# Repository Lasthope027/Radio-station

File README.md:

# 100 MHz FM Transmitter

## Overview

This repository contains the design and simulation files for a **100 MHz FM transmitter**, including the transmitter circuit, PCB design, manufacturing files, and a dedicated 100 MHz antenna design.

The project covers the workflow from **circuit simulation and PCB design to antenna modeling**.

For detailed technical specifications, design methodology, calculations, and simulation results, refer to the **[FM Radio Transmitter.pdf](FM%20Radio%20Transmitter.pdf)** included in this repository.

---

## Repository Structure

The repository is organized into the following sections:

- **Antenna/** — Contains the 100 MHz antenna model.
- **Transmitter/** — Contains the LTspice transmitter circuit and KiCad PCB design files.
- **FM Radio Transmitter.pdf** — Contains the detailed technical documentation and simulation results.
- **README.md** — Provides an overview and guide to the repository.

---

## Antenna

The `Antenna/` folder contains the antenna model designed specifically for operation at **100 MHz**.

### File

`FM Antenna.maa`

The `.maa` file can be opened using **MMANA-GAL** to inspect and simulate the antenna design.

**Software:** MMANA-GAL

---

## Transmitter

The `Transmitter/` folder contains the transmitter circuit and PCB design files.

### LTspice Circuit

The `Circuit .asc` file contains the transmitter schematic and can be opened using **LTspice** to inspect the circuit and reproduce the simulation.

**Software:** LTspice

### KiCad Files

The `KiCad/` folder contains the schematic, PCB layout, and manufacturing files.

- `RF Transmitter.kicad_sch` — KiCad schematic
- `RF Transmitter.kicad_pcb` — PCB layout
- `Gerber.zip` — Gerber files prepared for PCB fabrication

**Software:** KiCad

---

## Documentation

The `FM Radio Transmitter.pdf` contains the detailed technical documentation of the project, including the design, calculations, circuit analysis, simulation results, and antenna analysis.

For complete technical details, refer to the **[FM Radio Transmitter.pdf](FM%20Radio%20Transmitter.pdf)**.

---

## Software Used

| Software | Purpose |
|---|---|
| **LTspice** | Transmitter circuit design and simulation |
| **KiCad** | Schematic and PCB design |
| **MMANA-GAL** | 100 MHz antenna modeling and simulation |

---

## How to Explore the Repository

- To inspect the **transmitter circuit**, open the `.asc` file using LTspice.
- To inspect the **PCB schematic**, open the `.kicad_sch` file using KiCad.
- To inspect the **PCB layout**, open the `.kicad_pcb` file using KiCad.
- To fabricate the PCB, use the **Gerber.zip** manufacturing files.
- To inspect the **100 MHz antenna**, open the `.maa` file using MMANA-GAL.
- For detailed technical specifications, calculations, and simulation results, refer to the **FM Radio Transmitter PDF**.

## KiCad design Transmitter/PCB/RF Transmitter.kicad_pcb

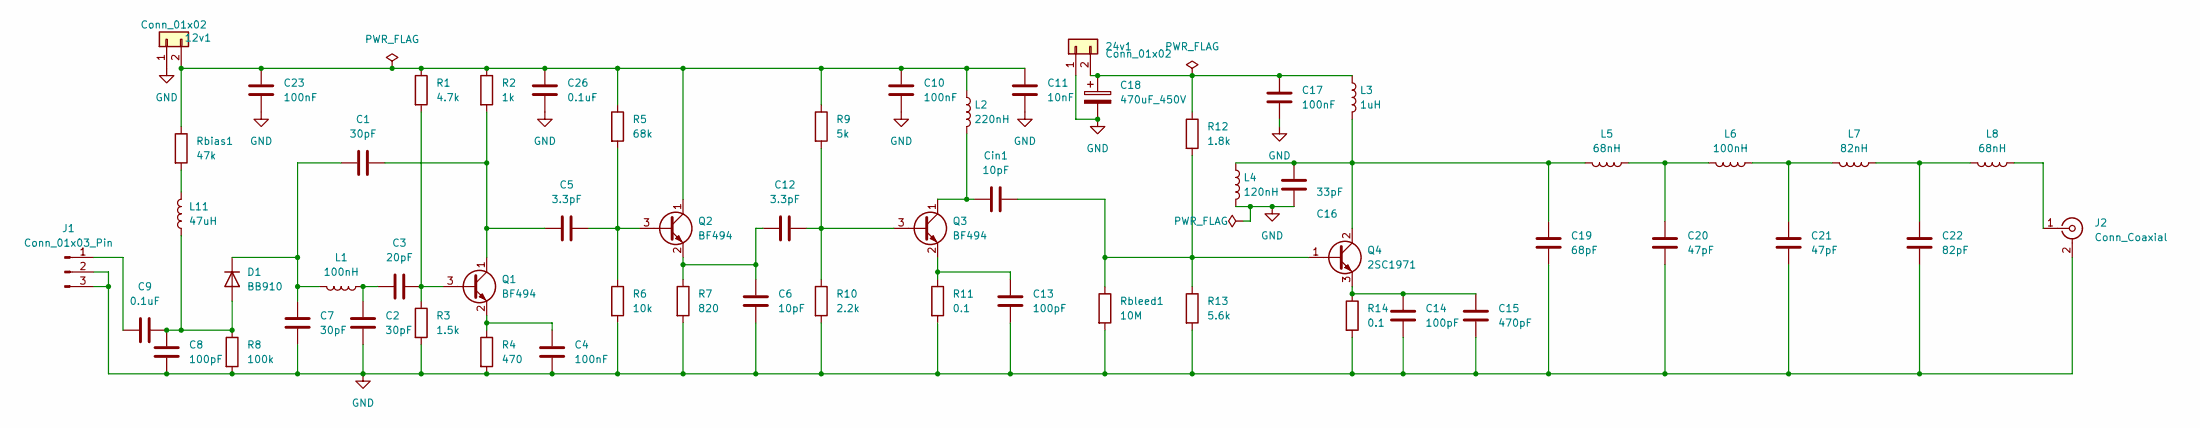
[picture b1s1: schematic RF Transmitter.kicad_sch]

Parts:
12v1, 24v1: Conn_01x02
C1, C2, C7: 30pF; C_0603_1608Metric
C3: 20pF; C_0603_1608Metric
C4, C10, C17, C23: 100nF; C_0805_2012Metric
C5, C12: 3.3pF; C_0603_1608Metric
C6: 10pF; C_0603_1608Metric
C8, C13, C14: 100pF; C_0603_1608Metric
C9, C26: 0.1uF; C_0805_2012Metric
C11: 10nF; C_0805_2012Metric
C15: 470pF; C_0603_1608Metric
C16: 33pF; C_0603_1608Metric
C18: 470uF_450V; CP_Radial_D10.0mm_P5.00mm
C19: 68pF; C_0603_1608Metric
C20, C21: 47pF; C_0603_1608Metric
C22: 82pF; C_0603_1608Metric
Cin1: 10pF; C_0603_1608Metric
D1: BB910; TO-92_Inline
J1: Conn_01x03_Pin; JST_PH_B3B-PH-K_1x03_P2.00mm_Vertical
J2: Conn_Coaxial; SMA_Amphenol_901-144_Vertical
L1, L6: 100nH; L_0603_1608Metric
L2: 220nH; L_0603_1608Metric
L3: 1uH; L_0805_2012Metric
L4: 120nH; L_0603_1608Metric
L5, L8: 68nH; L_0603_1608Metric
L7: 82nH; L_0603_1608Metric
L11: 47uH; L_0805_2012Metric
Q1, Q2, Q3: BF494; TO-92_Inline
Q4: 2SC1971; TO-220-3_Vertical
R1: 4.7k; R_Axial_DIN0207_L6.3mm_D2.5mm_P7.62mm_Horizontal
R2: 1k; R_Axial_DIN0207_L6.3mm_D2.5mm_P7.62mm_Horizontal
R3: 1.5k; R_Axial_DIN0207_L6.3mm_D2.5mm_P7.62mm_Horizontal
R4: 470; R_Axial_DIN0207_L6.3mm_D2.5mm_P7.62mm_Horizontal
R5: 68k; R_Axial_DIN0207_L6.3mm_D2.5mm_P7.62mm_Horizontal
R6: 10k; R_Axial_DIN0207_L6.3mm_D2.5mm_P7.62mm_Horizontal
R7: 820; R_Axial_DIN0207_L6.3mm_D2.5mm_P7.62mm_Horizontal
R8: 100k; R_Axial_DIN0207_L6.3mm_D2.5mm_P7.62mm_Horizontal
R9: 5k; R_Axial_DIN0207_L6.3mm_D2.5mm_P7.62mm_Horizontal
R10: 2.2k; R_Axial_DIN0207_L6.3mm_D2.5mm_P7.62mm_Horizontal
R11, R14: 0.1; R_Axial_DIN0411_L9.9mm_D3.6mm_P12.70mm_Horizontal
R12: 1.8k; R_Axial_DIN0207_L6.3mm_D2.5mm_P7.62mm_Horizontal
R13: 5.6k; R_Axial_DIN0207_L6.3mm_D2.5mm_P7.62mm_Horizontal
Rbias1: 47k; R_Axial_DIN0207_L6.3mm_D2.5mm_P7.62mm_Horizontal
Rbleed1: 10M; R_Axial_DIN0207_L6.3mm_D2.5mm_P7.62mm_Horizontal

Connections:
GND: 12v1.1, 24v1.1, C2.2, C4.2, C6.2, C7.2, C8.2, C10.2, C11.2, C13.2, C14.2, C15.2, C16.2, C17.2, C18.2, C19.2, C20.2, C21.2, C22.2, C23.2, C26.2, J1.2, J1.3, J2.2 (Ext), L4.2, R3.2, R4.2, R6.2, R7.2, R8.2, R10.2, R11.2, R13.2, R14.2, Rbleed1.2
unnamed: 12v1.2, C10.1, C11.1, C23.1, C26.1, L2.1, Q2.1 (C), R1.1, R2.1, R5.1, R9.1, Rbias1.1
unnamed: 24v1.2, C17.1, C18.1, L3.1, R12.1
unnamed: C2.1, C3.1, L1.1
unnamed: C20.1, L5.1, L6.2
unnamed: C21.1, L6.1, L7.2
unnamed: C22.1, L7.1, L8.2
unnamed: C8.1, C9.2, D1.2 (A), L11.1, R8.1
unnamed: C1.1, C7.1, D1.1 (K), L1.2
unnamed: C9.1, J1.1
unnamed: J2.1 (In), L8.1
unnamed: L11.2, Rbias1.2
unnamed: C3.2, Q1.3 (B), R1.2, R3.1
unnamed: C1.2, C5.1, Q1.1 (C), R2.2
unnamed: C4.1, Q1.2 (E), R4.1
unnamed: C5.2, Q2.3 (B), R5.2, R6.1
unnamed: C6.1, C12.1, Q2.2 (E), R7.1
unnamed: C12.2, Q3.3 (B), R9.2, R10.1
unnamed: Cin1.1, L2.2, Q3.1 (C)
unnamed: C13.1, Q3.2 (E), R11.1
unnamed: Cin1.2, Q4.1 (B), R12.2, R13.1, Rbleed1.1
unnamed: C16.1, C19.1, L3.2, L4.1, L5.2, Q4.2 (C)
unnamed: C14.1, C15.1, Q4.3 (E), R14.1

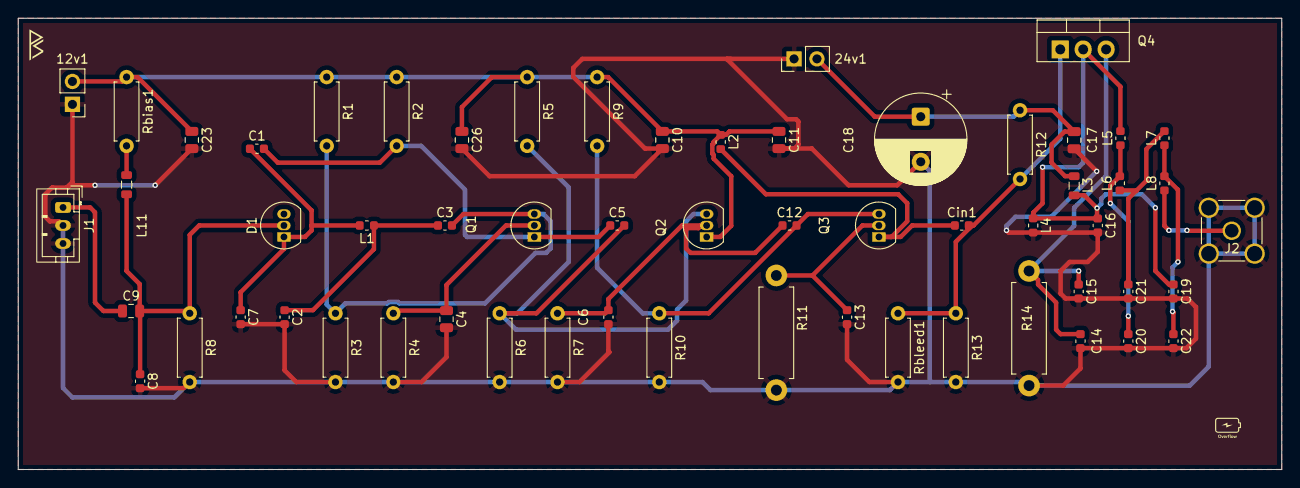
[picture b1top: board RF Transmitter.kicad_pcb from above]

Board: 2 copper layers, 140.0 x 50.0 mm, 59 parts (0 on the bottom side), 23 nets.
